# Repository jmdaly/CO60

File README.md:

# CO60 PCB

The CO60 was developed out of the desire to produce a 60% PCB that
appeals to many people and is readily available. CO60 is a portmanteau
of Community and 60% keyboard.

## Overview

The CO60 aims to meet the following design goals:

* Switches oriented such that the LEDs are South-facing, for
  compatibility with Cherry profile keycaps.

* USB Type-C support in both A to C and C to C configurations.

* QMK support.

* A variety of split spacebar configurations, including split 6.25U
  space and split 7U space.

* ESD protection circuitry, including data line protection and a
  polyfuse on the VCC line.

* Support for per-switch LED backlighting.

* Fits in standard 60% keyboard cases.

## Supported Layouts

The CO60 supports the [the following layouts](http://www.keyboard-layout-editor.com/#/gists/b488496b3a71c8192113c07e298be340).

## Motivation

There are a number of 60% keyboard PCBs available today, so it is important to
be clear about the reasons for developing a new one. This PCB is the only 60%
keyboard PCB that, to the best of my knowledge, satisfies ALL of the following
criteria:

* Support for MX switches oriented such that the LEDs are South
  facing, for compatibility with Cherry profile keycaps.

* Support for split spacebars, in both 6.25U and 7U configurations.

* USB Type-C connection that supports both A to C and C to C
  configurations.

* Open source hardware. This allows anybody to do a production run of the board
  at any point, and doesn't lock the design in with a particular vendor.

* QMK support.

* Based on an STM32F303 ARM MCU.

## Obtaining the Files

This repository contains several submodules, which in turn contain
KiCad libraries used in the PCB design. In order to clone the CO60
repository, and all of the library submodules, the following command
must be issued,

```
git clone --recursive https://github.com/jmdaly/CO60.git
```

## Acknowledgements

This PCB design would not have been possible without the help and previous work
of a number of people. In particular, great inspiration has been derived from
the [GH60 project](https://github.com/komar007/gh60), and [ai03's excellent
open source keyboard designs](https://github.com/ai03-2725). This includes the
use of ai03's KiCad [switch footprint
libraries](https://github.com/ai03-2725/MX_Alps_Hybrid.pretty) and his [USB
Type-C](https://github.com/ai03-2725/Type-C.pretty) KiCad footprint libraries.

The Banana Split V2 PCB provided inspiration for some of the bottom row
layouts. The Banana Split was the first 60% PCB to popularize the split
spacebar layout, and the folks at [The Van
Keyboards](https://thevankeyboards.com/) deserve a lot of credit for this
development.

The board outline libraries were created by amtra5, and full credit
goes to him for their design.

There is an active keyboard design community on the MechKeys discord. The
users there have been very helpful, and I've learned a significant
amount about PCB design from them.

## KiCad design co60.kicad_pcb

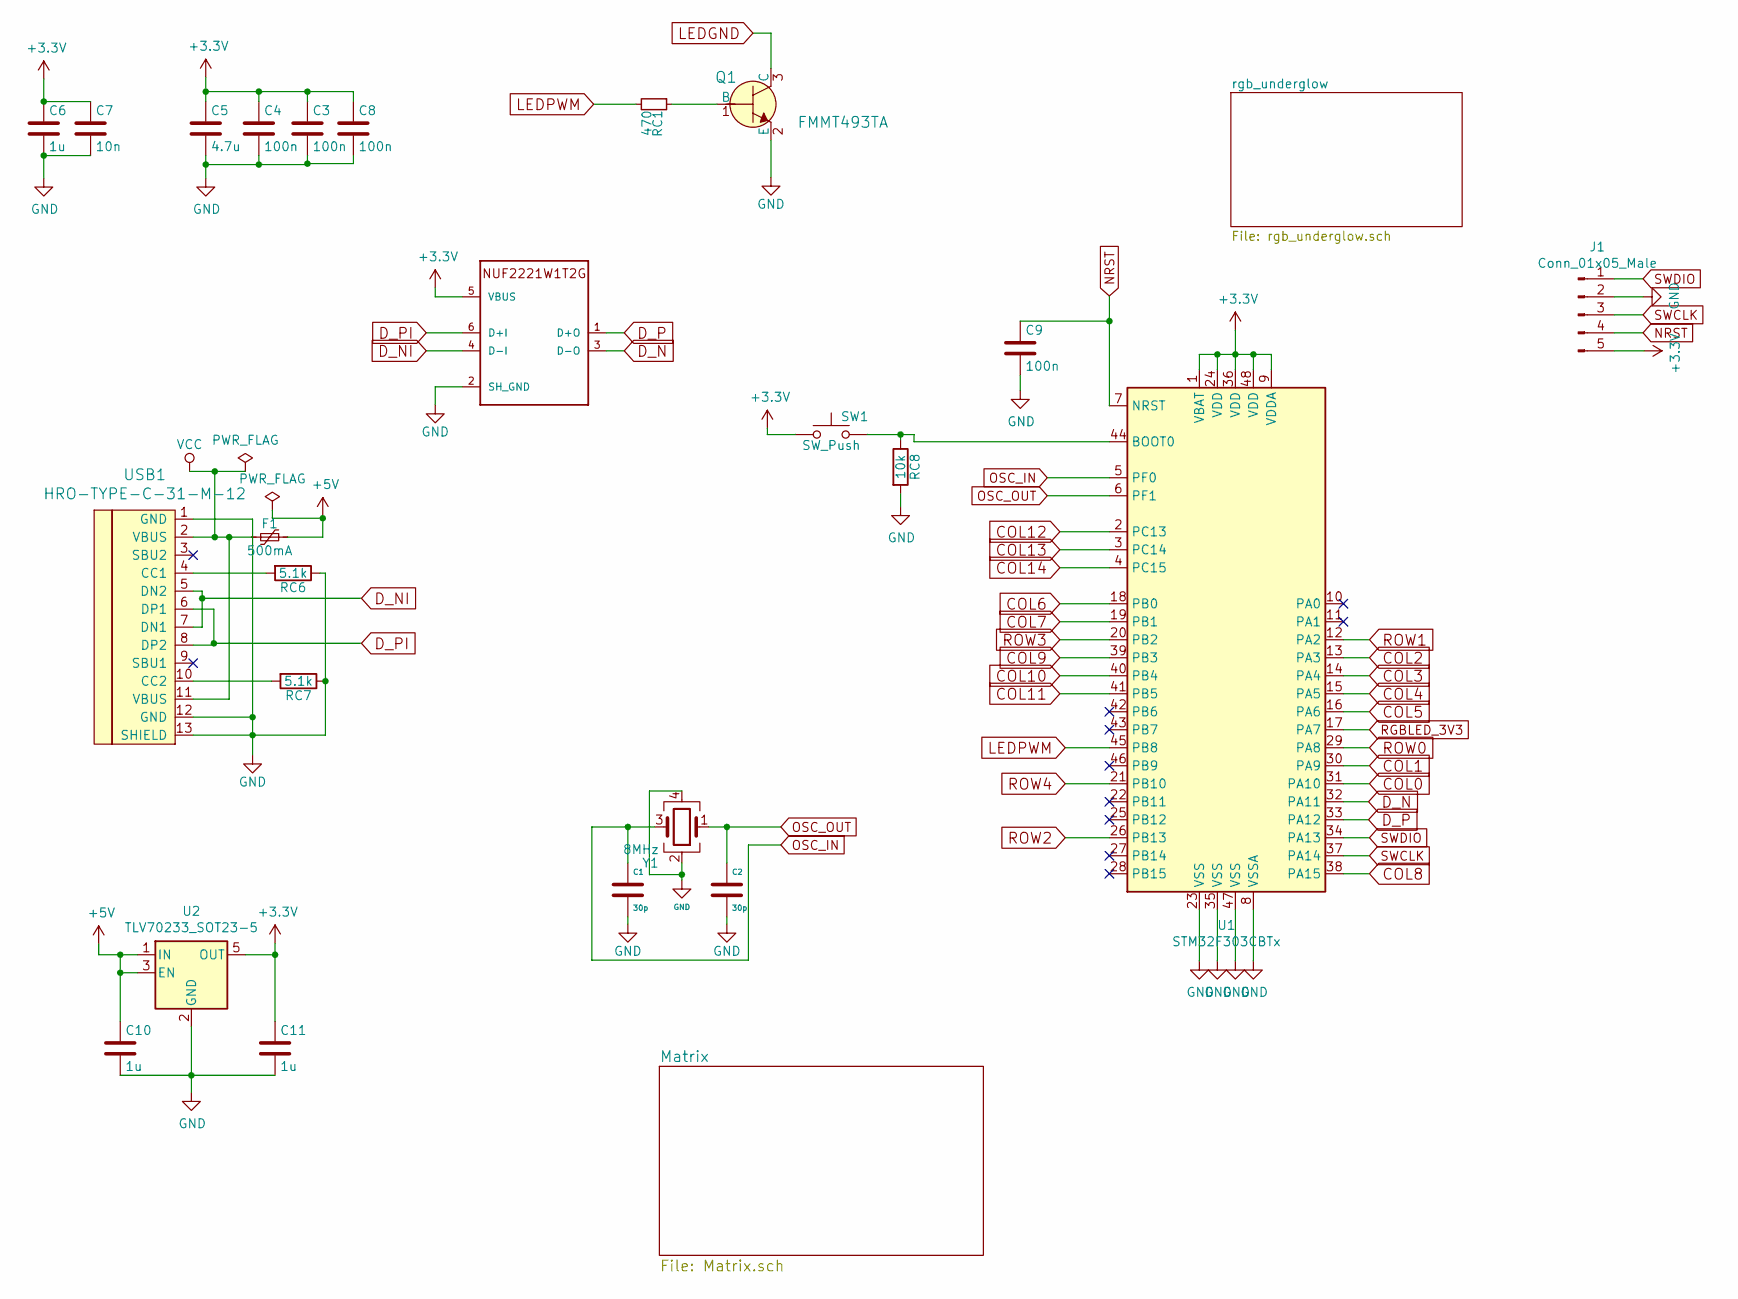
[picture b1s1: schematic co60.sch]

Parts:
C1, C2: 30p; C_0603_1608Metric; LCSC PN C22397
C3, C4, C8, C9: 100n; C_0603_1608Metric; Digi-Key_PN 445-2500-1-ND
C5: 4.7u; C_0603_1608Metric; Digi-Key_PN 1276-1900-1-ND
C6, C10, C11: 1u; C_0603_1608Metric; Digi-Key_PN 445-13234-1-ND
C7: 10n; C_0603_1608Metric; LCSC PN C1589
F1: 500mA; R_0805; Digi-Key_PN F2772CT-ND
J1: Conn_01x05_Male; PinHeader_1x05_P2.54mm_Vertical
Q1: FMMT493TA; SOT-23-3; MPN FMMT493TA; Digi-Key_PN FMMT493CT-ND
RC1: 470; R_0603_1608Metric; LCSC PN C114433
RC6: 5.1k; R_0603; Digi-Key_PN RMCF0603JT5K10CT-ND
RC7: 5.1k; R_0603; LCSC PN C14677
RC8: 10k; R_0603; Digi-Key_PN P10KGCT-ND
SW1: SW_Push; SW_SPST_TL3342; Digi-Key_PN EG2531CT-ND
U1: STM32F303CBTx; LQFP-48_7x7mm_Pitch0.5mm; LCSC PN C108516
U2: TLV70233_SOT23-5; SOT-23-5; LCSC PN C26833
U3: NUF2221W1T2G; SOT-363; LCSC PN C274624
USB1: HRO-TYPE-C-31-M-12; HRO-TYPE-C-31-M-12-Assembly; LCSC PN C165948
Y1: 8MHz; Crystal_SMD_5032-4pin_5.0x3.2mm; LCSC PN C133333

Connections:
+3V3: C3.1, C4.1, C5.1, C6.1, C7.1, C8.1, C11.1, J1.5, SW1.1, U1.1 (VBAT), U1.9 (VDDA), U1.24 (VDD), U1.36 (VDD), U1.48 (VDD), U2.5 (OUT), U3.5 (VBUS)
+5V: C10.1, F1.1, U2.1 (IN), U2.3 (EN); also elsewhere on the board
COL0: U1.31 (PA10); also elsewhere on the board
COL1: U1.30 (PA9); also elsewhere on the board
COL2: U1.13 (PA3); also elsewhere on the board
COL3: U1.14 (PA4); also elsewhere on the board
COL4: U1.15 (PA5); also elsewhere on the board
COL5: U1.16 (PA6); also elsewhere on the board
COL6: U1.18 (PB0); also elsewhere on the board
COL7: U1.19 (PB1); also elsewhere on the board
COL8: U1.38 (PA15); also elsewhere on the board
COL9: U1.39 (PB3); also elsewhere on the board
COL10: U1.40 (PB4); also elsewhere on the board
COL11: U1.41 (PB5); also elsewhere on the board
COL12: U1.2 (PC13); also elsewhere on the board
COL13: U1.3 (PC14); also elsewhere on the board
COL14: U1.4 (PC15); also elsewhere on the board
D_N: U1.32 (PA11), U3.3 (D-O)
D_NI: U3.4 (D-I), USB1.5 (DN2), USB1.7 (DN1)
D_P: U1.33 (PA12), U3.1 (D+O)
D_PI: U3.6 (D+I), USB1.6 (DP1), USB1.8 (DP2)
GND: C1.2, C2.2, C3.2, C4.2, C5.2, C6.2, C7.2, C8.2, C9.2, C10.2, C11.2, J1.2, Q1.2 (E), RC6.1, RC7.1, RC8.2, U1.8 (VSSA), U1.23 (VSS), U1.35 (VSS), U1.47 (VSS), U2.2 (GND), U3.2 (SH_GND), USB1.1 (GND), USB1.12 (GND), USB1.13 (SHIELD), Y1.2, Y1.4; also elsewhere on the board
LEDGND: Q1.3 (C); also elsewhere on the board
LEDPWM: RC1.2, U1.45 (PB8)
NRST: C9.1, J1.4, U1.7 (NRST)
unnamed: Q1.1 (B), RC1.1
unnamed: RC6.2, USB1.4 (CC1)
unnamed: RC7.2, USB1.10 (CC2)
unnamed: RC8.1, SW1.2, U1.44 (BOOT0)
OSC_IN: C1.1, U1.5 (PF0), Y1.3
OSC_OUT: C2.1, U1.6 (PF1), Y1.1
RGBLED_3V3: U1.17 (PA7); also elsewhere on the board
ROW0: U1.29 (PA8); also elsewhere on the board
ROW1: U1.12 (PA2); also elsewhere on the board
ROW2: U1.26 (PB13); also elsewhere on the board
ROW3: U1.20 (PB2); also elsewhere on the board
ROW4: U1.21 (PB10); also elsewhere on the board
SWCLK: J1.3, U1.37 (PA14)
SWDIO: J1.1, U1.34 (PA13)
VCC: F1.2, USB1.2 (VBUS), USB1.11 (VBUS)

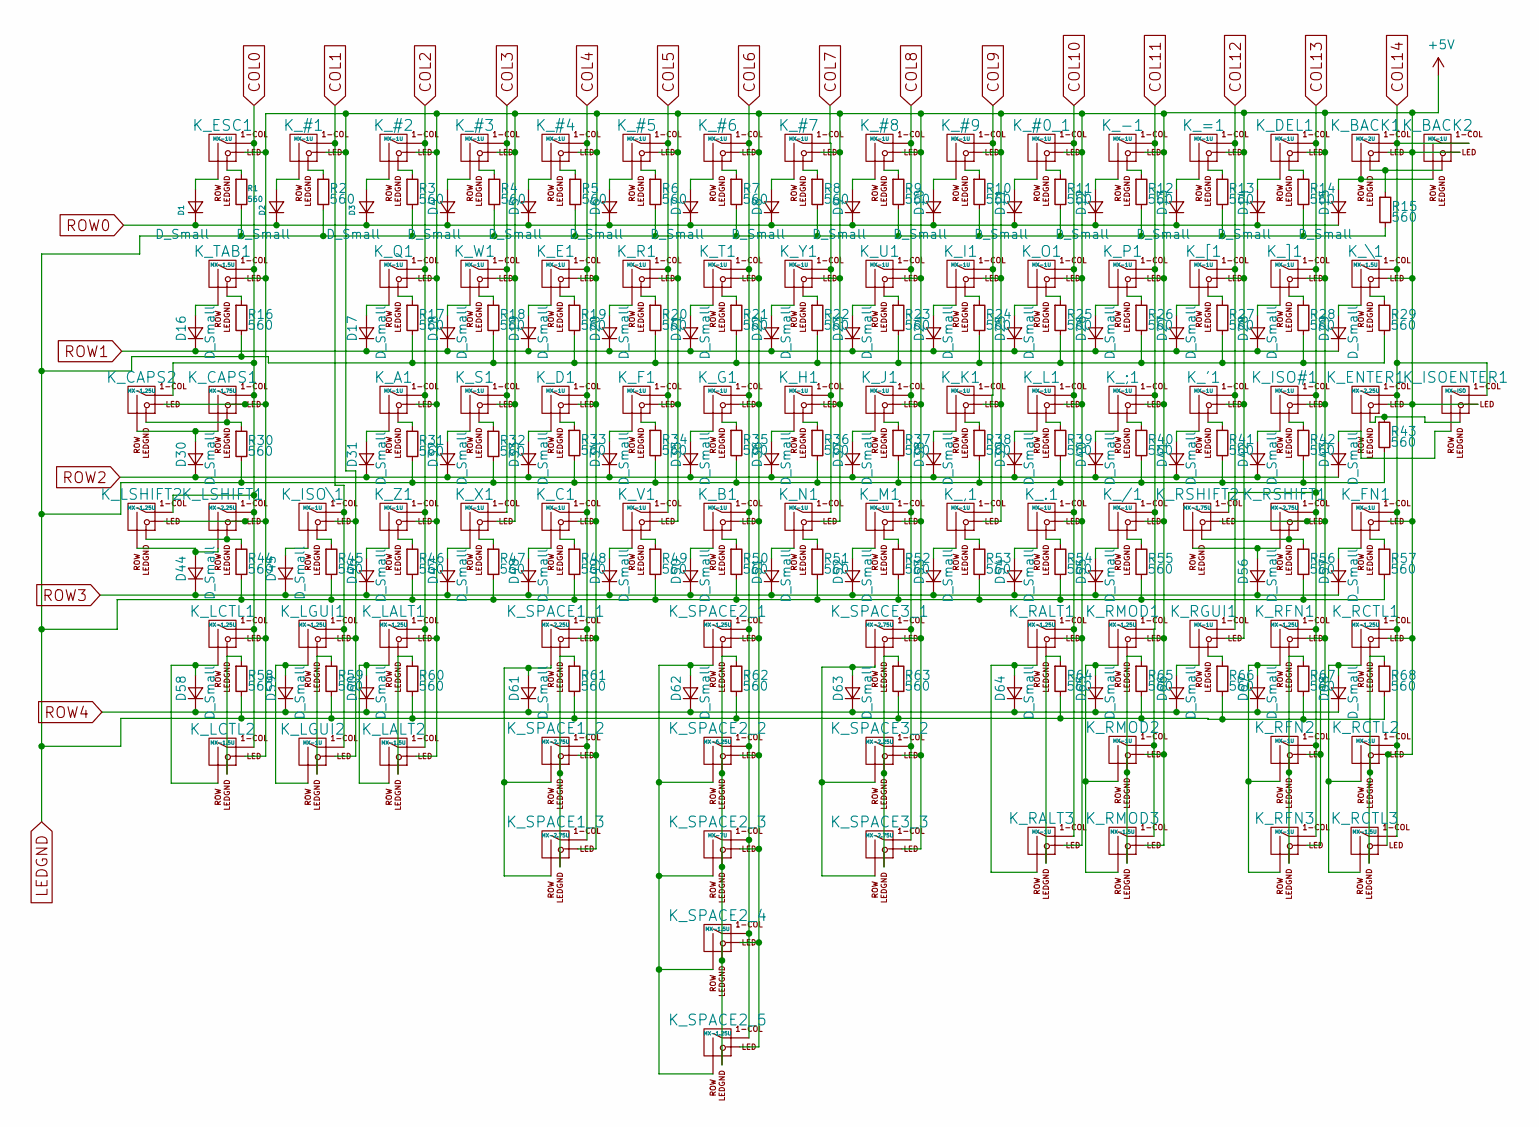
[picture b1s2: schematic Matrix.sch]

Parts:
D1: D_Small; D_SOD-123; Digi-Key_PN 1N4148WTPMSCT-ND
D2, D3, D4, D5, D6, D7, D8, D9, D10, D11, D12, D13, D14, D15, D16, D17, D18, D19, D20, D21, D22, D23, D24, D25, D26, D27, D28, D29, D30, D31, D32, D33, D34, D35, D36, D37, D38, D39, D40, D41, D42, D43, D44, D45, D46, D47, D48, D49, D50, D51, D52, D53, D54, D55, D56, D57, D58, D59, D60, D61, D62, D63, D64, D65, D66, D67, D68: D_Small; D_SOD-123
K_#0_1, K_#1, K_#2, K_#3, K_#4, K_#5, K_#6, K_#7, K_#8, K_#9: MX-1U; MXOnly-1U-FLIPPED
K_'1: MX-1U; MXOnly-1U-FLIPPED
K_,1: MX-1U; MXOnly-1U-FLIPPED
K_-1: MX-1U; MXOnly-1U-FLIPPED
K_.1: MX-1U; MXOnly-1U-FLIPPED
K_/1: MX-1U; MXOnly-1U-FLIPPED
K_;1: MX-1U; MXOnly-1U-FLIPPED
K_=1: MX-1U; MXOnly-1U-FLIPPED
K_A1: MX-1U; MXOnly-1U-FLIPPED
K_B1: MX-1U; MXOnly-1U-FLIPPED
K_BACK1: MX-2U; MXOnly-2U-FLIPPED
K_BACK2: MX-1U; MXOnly-1U-FLIPPED
K_C1: MX-1U; MXOnly-1U-FLIPPED
K_CAPS1: MX-1.75U; MXOnly-1.75U
K_CAPS2: MX-1.25U; MXOnly-1.25U-FLIPPED
K_D1: MX-1U; MXOnly-1U-FLIPPED
K_DEL1: MX-1U; MXOnly-1U-FLIPPED
K_E1: MX-1U; MXOnly-1U-FLIPPED
K_ENTER1: MX-2.25U; MXOnly-2.25U-FLIPPED
K_ESC1: MX-1U; MXOnly-1U-FLIPPED
K_F1: MX-1U; MXOnly-1U-FLIPPED
K_FN1: MX-1U; MXOnly-1U-FLIPPED
K_G1: MX-1U; MXOnly-1U-FLIPPED
K_H1: MX-1U; MXOnly-1U-FLIPPED
K_I1: MX-1U; MXOnly-1U-FLIPPED
K_ISO#1: MX-1U; MXOnly-1U-FLIPPED
K_ISOENTER1: MX-ISO; MXOnly-ISO-ROTATED-ReversedStabilizers
K_ISO\1: MX-1U; MXOnly-1U-FLIPPED
K_J1: MX-1U; MXOnly-1U-FLIPPED
K_K1: MX-1U; MXOnly-1U-FLIPPED
K_L1: MX-1U; MXOnly-1U-FLIPPED
K_LALT1: MX-1.25U; MXOnly-1.25U-FLIPPED
K_LALT2: MX-1.5U; MXOnly-1.5U
K_LCTL1: MX-1.25U; MXOnly-1.25U-FLIPPED
K_LCTL2: MX-1.5U; MXOnly-1.5U
K_LGUI1: MX-1.25U; MXOnly-1.25U-FLIPPED
K_LGUI2: MX-1U; MXOnly-1U
K_LSHIFT1: MX-2.25U; MXOnly-2.25U-FLIPPED
K_LSHIFT2: MX-1.25U; MXOnly-1.25U-FLIPPED
K_M1: MX-1U; MXOnly-1U-FLIPPED
K_N1: MX-1U; MXOnly-1U-FLIPPED
K_O1: MX-1U; MXOnly-1U-FLIPPED
K_P1: MX-1U; MXOnly-1U-FLIPPED
K_Q1: MX-1U; MXOnly-1U-FLIPPED
K_R1: MX-1U; MXOnly-1U-FLIPPED
K_RALT1: MX-1.25U; MXOnly-1.25U-FLIPPED
K_RALT3: MX-1U; MXOnly-1U
K_RCTL1: MX-1.25U; MXOnly-1.25U-FLIPPED
K_RCTL2: MX-1U; MXOnly-1U
K_RCTL3: MX-1.5U; MXOnly-1.5U
K_RFN1: MX-1.25U; MXOnly-1.25U-FLIPPED
K_RFN2, K_RFN3: MX-1U; MXOnly-1U
K_RGUI1: MX-1U; MXOnly-1U-FLIPPED
K_RMOD1: MX-1.25U; MXOnly-1.25U
K_RMOD2: MX-1U; MXOnly-1U
K_RMOD3: MX-1.5U; MXOnly-1.5U-FLIPPED
K_RSHIFT1: MX-2.75U; MXOnly-2.75U-FLIPPED
K_RSHIFT2: MX-1.75U; MXOnly-1.75U-FLIPPED
K_S1: MX-1U; MXOnly-1U-FLIPPED
K_SPACE1_1, K_SPACE3_2: MX-2.25U; MXOnly-2.25U-ReversedStabilizers
K_SPACE1_2, K_SPACE3_1: MX-2.75U; MXOnly-2.75U-FLIPPED-ReversedStabilizers
K_SPACE1_3, K_SPACE3_3: MX-2.75U; MXOnly-2.75U-ReversedStabilizers
K_SPACE2_1, K_SPACE2_5: MX-1.25U; MXOnly-1.25U-FLIPPED
K_SPACE2_2: MX-6.25U; MXOnly-6.25U-ReversedStabilizers
K_SPACE2_3: MX-7U; MXOnly-7U-ReversedStabilizers
K_SPACE2_4: MX-1.5U; MXOnly-1.5U
K_T1: MX-1U; MXOnly-1U-FLIPPED
K_TAB1: MX-1.5U; MXOnly-1.5U-FLIPPED
K_U1: MX-1U; MXOnly-1U-FLIPPED
K_V1: MX-1U; MXOnly-1U-FLIPPED
K_W1: MX-1U; MXOnly-1U-FLIPPED
K_X1: MX-1U; MXOnly-1U-FLIPPED
K_Y1: MX-1U; MXOnly-1U-FLIPPED
K_Z1: MX-1U; MXOnly-1U-FLIPPED
K_[1: MX-1U; MXOnly-1U-FLIPPED
K_\1: MX-1.5U; MXOnly-1.5U-FLIPPED
K_]1: MX-1U; MXOnly-1U-FLIPPED
R1: 560; R_0603; Digi-Key_PN MCT0603-560-CFCT-ND
R2, R3, R4, R5, R6, R7, R8, R9, R10, R11, R12, R13, R14, R15, R16, R17, R18, R19, R20, R21, R22, R23, R24, R25, R26, R27, R28, R29, R30, R31, R32, R33, R34, R35, R36, R37, R38, R39, R40, R41, R42, R43, R44, R45, R46, R47, R48, R49, R50, R51, R52, R53, R54, R55, R56, R57, R58, R59, R60, R61, R62, R63, R64, R65, R66, R67, R68: 560; R_0603

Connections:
+5V: K_#0_1.3 (LED), K_#1.3 (LED), K_#2.3 (LED), K_#3.3 (LED), K_#4.3 (LED), K_#5.3 (LED), K_#6.3 (LED), K_#7.3 (LED), K_#8.3 (LED), K_#9.3 (LED), K_'1.3 (LED), K_,1.3 (LED), K_-1.3 (LED), K_.1.3 (LED), K_/1.3 (LED), K_;1.3 (LED), K_=1.3 (LED), K_A1.3 (LED), K_B1.3 (LED), K_BACK1.3 (LED), K_BACK2.3 (LED), K_C1.3 (LED), K_CAPS1.3 (LED), K_CAPS2.3 (LED), K_D1.3 (LED), K_DEL1.3 (LED), K_E1.3 (LED), K_ENTER1.3 (LED), K_ESC1.3 (LED), K_F1.3 (LED), K_FN1.3 (LED), K_G1.3 (LED), K_H1.3 (LED), K_I1.3 (LED), K_ISO#1.3 (LED), K_ISOENTER1.3 (LED), K_ISO\1.3 (LED), K_J1.3 (LED), K_K1.3 (LED), K_L1.3 (LED), K_LALT1.3 (LED), K_LALT2.3 (LED), K_LCTL1.3 (LED), K_LCTL2.3 (LED), K_LGUI1.3 (LED), K_LGUI2.3 (LED), K_LSHIFT1.3 (LED), K_LSHIFT2.3 (LED), K_M1.3 (LED), K_N1.3 (LED), K_O1.3 (LED), K_P1.3 (LED), K_Q1.3 (LED), K_R1.3 (LED), K_RALT1.3 (LED), K_RALT3.3 (LED), K_RCTL1.3 (LED), K_RCTL2.3 (LED), K_RCTL3.3 (LED), K_RFN1.3 (LED), K_RFN2.3 (LED), K_RFN3.3 (LED), K_RGUI1.3 (LED), K_RMOD1.3 (LED), K_RMOD2.3 (LED), K_RMOD3.3 (LED), K_RSHIFT1.3 (LED), K_RSHIFT2.3 (LED), K_S1.3 (LED), K_SPACE1_1.3 (LED), K_SPACE1_2.3 (LED), K_SPACE1_3.3 (LED), K_SPACE2_1.3 (LED), K_SPACE2_2.3 (LED), K_SPACE2_3.3 (LED), K_SPACE2_4.3 (LED), K_SPACE2_5.3 (LED), K_SPACE3_1.3 (LED), K_SPACE3_2.3 (LED), K_SPACE3_3.3 (LED), K_T1.3 (LED), K_TAB1.3 (LED), K_U1.3 (LED), K_V1.3 (LED), K_W1.3 (LED), K_X1.3 (LED), K_Y1.3 (LED), K_Z1.3 (LED), K_[1.3 (LED), K_\1.3 (LED), K_]1.3 (LED); also elsewhere on the board
COL0: K_CAPS1.1 (COL), K_CAPS2.1 (COL), K_ESC1.1 (COL), K_LCTL1.1 (COL), K_LCTL2.1 (COL), K_LSHIFT1.1 (COL), K_LSHIFT2.1 (COL), K_TAB1.1 (COL); also elsewhere on the board
COL1: K_#1.1 (COL), K_ISO\1.1 (COL), K_LGUI1.1 (COL), K_LGUI2.1 (COL); also elsewhere on the board
COL2: K_#2.1 (COL), K_A1.1 (COL), K_LALT1.1 (COL), K_LALT2.1 (COL), K_Q1.1 (COL), K_Z1.1 (COL); also elsewhere on the board
COL3: K_#3.1 (COL), K_S1.1 (COL), K_W1.1 (COL), K_X1.1 (COL); also elsewhere on the board
COL4: K_#4.1 (COL), K_C1.1 (COL), K_D1.1 (COL), K_E1.1 (COL), K_SPACE1_1.1 (COL), K_SPACE1_2.1 (COL), K_SPACE1_3.1 (COL); also elsewhere on the board
COL5: K_#5.1 (COL), K_F1.1 (COL), K_R1.1 (COL), K_V1.1 (COL); also elsewhere on the board
COL6: K_#6.1 (COL), K_B1.1 (COL), K_G1.1 (COL), K_SPACE2_1.1 (COL), K_SPACE2_2.1 (COL), K_SPACE2_3.1 (COL), K_SPACE2_4.1 (COL), K_SPACE2_5.1 (COL), K_T1.1 (COL); also elsewhere on the board
COL7: K_#7.1 (COL), K_H1.1 (COL), K_N1.1 (COL), K_Y1.1 (COL); also elsewhere on the board
COL8: K_#8.1 (COL), K_J1.1 (COL), K_M1.1 (COL), K_SPACE3_1.1 (COL), K_SPACE3_2.1 (COL), K_SPACE3_3.1 (COL), K_U1.1 (COL); also elsewhere on the board
COL9: K_#9.1 (COL), K_,1.1 (COL), K_I1.1 (COL), K_K1.1 (COL); also elsewhere on the board
COL10: K_#0_1.1 (COL), K_.1.1 (COL), K_L1.1 (COL), K_O1.1 (COL), K_RALT1.1 (COL), K_RALT3.1 (COL); also elsewhere on the board
COL11: K_-1.1 (COL), K_/1.1 (COL), K_;1.1 (COL), K_P1.1 (COL), K_RMOD1.1 (COL), K_RMOD2.1 (COL), K_RMOD3.1 (COL); also elsewhere on the board
COL12: K_'1.1 (COL), K_=1.1 (COL), K_RGUI1.1 (COL), K_[1.1 (COL); also elsewhere on the board
COL13: K_DEL1.1 (COL), K_ISO#1.1 (COL), K_RFN1.1 (COL), K_RFN2.1 (COL), K_RFN3.1 (COL), K_RSHIFT1.1 (COL), K_RSHIFT2.1 (COL), K_]1.1 (COL); also elsewhere on the board
COL14: K_BACK1.1 (COL), K_BACK2.1 (COL), K_ENTER1.1 (COL), K_FN1.1 (COL), K_ISOENTER1.1 (COL), K_RCTL1.1 (COL), K_RCTL2.1 (COL), K_RCTL3.1 (COL), K_\1.1 (COL); also elsewhere on the board
LEDGND: R1.2, R2.2, R3.2, R4.2, R5.2, R6.2, R7.2, R8.2, R9.2, R10.2, R11.2, R12.2, R13.2, R14.2, R15.2, R16.2, R17.2, R18.2, R19.2, R20.2, R21.2, R22.2, R23.2, R24.2, R25.2, R26.2, R27.2, R28.2, R29.2, R30.2, R31.2, R32.2, R33.2, R34.2, R35.2, R36.2, R37.2, R38.2, R39.2, R40.2, R41.2, R42.2, R43.2, R44.2, R45.2, R46.2, R47.2, R48.2, R49.2, R50.2, R51.2, R52.2, R53.2, R54.2, R55.2, R56.2, R57.2, R58.2, R59.2, R60.2, R61.2, R62.2, R63.2, R64.2, R65.2, R66.2, R67.2, R68.2; also elsewhere on the board
unnamed: D1.2 (A), K_ESC1.2 (ROW)
unnamed: D2.2 (A), K_#1.2 (ROW)
unnamed: D3.2 (A), K_#2.2 (ROW)
unnamed: D4.2 (A), K_#3.2 (ROW)
unnamed: D5.2 (A), K_#4.2 (ROW)
unnamed: D6.2 (A), K_#5.2 (ROW)
unnamed: D7.2 (A), K_#6.2 (ROW)
unnamed: D8.2 (A), K_#7.2 (ROW)
unnamed: D9.2 (A), K_#8.2 (ROW)
unnamed: D10.2 (A), K_#9.2 (ROW)
unnamed: D11.2 (A), K_#0_1.2 (ROW)
unnamed: D12.2 (A), K_-1.2 (ROW)
unnamed: D13.2 (A), K_=1.2 (ROW)
unnamed: D14.2 (A), K_DEL1.2 (ROW)
unnamed: D15.2 (A), K_BACK1.2 (ROW), K_BACK2.2 (ROW)
unnamed: D16.2 (A), K_TAB1.2 (ROW)
unnamed: D17.2 (A), K_Q1.2 (ROW)
unnamed: D18.2 (A), K_W1.2 (ROW)
unnamed: D19.2 (A), K_E1.2 (ROW)
unnamed: D20.2 (A), K_R1.2 (ROW)
unnamed: D21.2 (A), K_T1.2 (ROW)
unnamed: D22.2 (A), K_Y1.2 (ROW)
unnamed: D23.2 (A), K_U1.2 (ROW)
unnamed: D24.2 (A), K_I1.2 (ROW)
unnamed: D25.2 (A), K_O1.2 (ROW)
unnamed: D26.2 (A), K_P1.2 (ROW)
unnamed: D27.2 (A), K_[1.2 (ROW)
unnamed: D28.2 (A), K_]1.2 (ROW)
unnamed: D29.2 (A), K_\1.2 (ROW)
unnamed: D30.2 (A), K_CAPS1.2 (ROW), K_CAPS2.2 (ROW)
unnamed: D31.2 (A), K_A1.2 (ROW)
unnamed: D32.2 (A), K_S1.2 (ROW)
unnamed: D33.2 (A), K_D1.2 (ROW)
unnamed: D34.2 (A), K_F1.2 (ROW)
unnamed: D35.2 (A), K_G1.2 (ROW)
unnamed: D36.2 (A), K_H1.2 (ROW)
unnamed: D37.2 (A), K_J1.2 (ROW)
unnamed: D38.2 (A), K_K1.2 (ROW)
unnamed: D39.2 (A), K_L1.2 (ROW)
unnamed: D40.2 (A), K_;1.2 (ROW)
unnamed: D41.2 (A), K_'1.2 (ROW)
unnamed: D42.2 (A), K_ISO#1.2 (ROW)
unnamed: D43.2 (A), K_ENTER1.2 (ROW), K_ISOENTER1.2 (ROW)
unnamed: D44.2 (A), K_LSHIFT1.2 (ROW), K_LSHIFT2.2 (ROW)
unnamed: D45.2 (A), K_ISO\1.2 (ROW)
unnamed: D46.2 (A), K_Z1.2 (ROW)
unnamed: D47.2 (A), K_X1.2 (ROW)
unnamed: D48.2 (A), K_C1.2 (ROW)
unnamed: D49.2 (A), K_V1.2 (ROW)
unnamed: D50.2 (A), K_B1.2 (ROW)
unnamed: D51.2 (A), K_N1.2 (ROW)
unnamed: D52.2 (A), K_M1.2 (ROW)
unnamed: D53.2 (A), K_,1.2 (ROW)
unnamed: D54.2 (A), K_.1.2 (ROW)
unnamed: D55.2 (A), K_/1.2 (ROW)
unnamed: D56.2 (A), K_RSHIFT1.2 (ROW), K_RSHIFT2.2 (ROW)
unnamed: D57.2 (A), K_FN1.2 (ROW)
unnamed: D58.2 (A), K_LCTL1.2 (ROW), K_LCTL2.2 (ROW)
unnamed: D59.2 (A), K_LGUI1.2 (ROW), K_LGUI2.2 (ROW)
unnamed: D60.2 (A), K_LALT1.2 (ROW), K_LALT2.2 (ROW)
unnamed: D61.2 (A), K_SPACE1_1.2 (ROW), K_SPACE1_2.2 (ROW), K_SPACE1_3.2 (ROW)
unnamed: D62.2 (A), K_SPACE2_1.2 (ROW), K_SPACE2_2.2 (ROW), K_SPACE2_3.2 (ROW), K_SPACE2_4.2 (ROW), K_SPACE2_5.2 (ROW)
unnamed: D63.2 (A), K_SPACE3_1.2 (ROW), K_SPACE3_2.2 (ROW), K_SPACE3_3.2 (ROW)
unnamed: D64.2 (A), K_RALT1.2 (ROW), K_RALT3.2 (ROW)
unnamed: D65.2 (A), K_RMOD1.2 (ROW), K_RMOD2.2 (ROW), K_RMOD3.2 (ROW)
unnamed: D66.2 (A), K_RGUI1.2 (ROW)
unnamed: D67.2 (A), K_RFN1.2 (ROW), K_RFN2.2 (ROW), K_RFN3.2 (ROW)
unnamed: D68.2 (A), K_RCTL1.2 (ROW), K_RCTL2.2 (ROW), K_RCTL3.2 (ROW)
unnamed: K_#0_1.4 (LEDGND), R11.1
unnamed: K_#1.4 (LEDGND), R2.1
unnamed: K_#2.4 (LEDGND), R3.1
unnamed: K_#3.4 (LEDGND), R4.1
unnamed: K_#4.4 (LEDGND), R5.1
unnamed: K_#5.4 (LEDGND), R6.1
unnamed: K_#6.4 (LEDGND), R7.1
unnamed: K_#7.4 (LEDGND), R8.1
unnamed: K_#8.4 (LEDGND), R9.1
unnamed: K_#9.4 (LEDGND), R10.1
unnamed: K_'1.4 (LEDGND), R41.1
unnamed: K_,1.4 (LEDGND), R53.1
unnamed: K_-1.4 (LEDGND), R12.1
unnamed: K_.1.4 (LEDGND), R54.1
unnamed: K_/1.4 (LEDGND), R55.1
unnamed: K_;1.4 (LEDGND), R40.1
unnamed: K_=1.4 (LEDGND), R13.1
unnamed: K_A1.4 (LEDGND), R31.1
unnamed: K_B1.4 (LEDGND), R50.1
unnamed: K_BACK1.4 (LEDGND), K_BACK2.4 (LEDGND), R15.1
unnamed: K_C1.4 (LEDGND), R48.1
unnamed: K_CAPS1.4 (LEDGND), K_CAPS2.4 (LEDGND), R30.1
unnamed: K_D1.4 (LEDGND), R33.1
unnamed: K_DEL1.4 (LEDGND), R14.1
unnamed: K_E1.4 (LEDGND), R19.1
unnamed: K_ENTER1.4 (LEDGND), K_ISOENTER1.4 (LEDGND), R43.1
unnamed: K_ESC1.4 (LEDGND), R1.1
unnamed: K_F1.4 (LEDGND), R34.1
unnamed: K_FN1.4 (LEDGND), R57.1
unnamed: K_G1.4 (LEDGND), R35.1
unnamed: K_H1.4 (LEDGND), R36.1
unnamed: K_I1.4 (LEDGND), R24.1
unnamed: K_ISO#1.4 (LEDGND), R42.1
unnamed: K_ISO\1.4 (LEDGND), R45.1
unnamed: K_J1.4 (LEDGND), R37.1
unnamed: K_K1.4 (LEDGND), R38.1
unnamed: K_L1.4 (LEDGND), R39.1
unnamed: K_LALT1.4 (LEDGND), K_LALT2.4 (LEDGND), R60.1
unnamed: K_LCTL1.4 (LEDGND), K_LCTL2.4 (LEDGND), R58.1
unnamed: K_LGUI1.4 (LEDGND), K_LGUI2.4 (LEDGND), R59.1
unnamed: K_LSHIFT1.4 (LEDGND), K_LSHIFT2.4 (LEDGND), R44.1
unnamed: K_M1.4 (LEDGND), R52.1
unnamed: K_N1.4 (LEDGND), R51.1
unnamed: K_O1.4 (LEDGND), R25.1
unnamed: K_P1.4 (LEDGND), R26.1
unnamed: K_Q1.4 (LEDGND), R17.1
unnamed: K_R1.4 (LEDGND), R20.1
unnamed: K_RALT1.4 (LEDGND), K_RALT3.4 (LEDGND), R64.1
unnamed: K_RCTL1.4 (LEDGND), K_RCTL2.4 (LEDGND), K_RCTL3.4 (LEDGND), R68.1
unnamed: K_RFN1.4 (LEDGND), K_RFN2.4 (LEDGND), K_RFN3.4 (LEDGND), R67.1
unnamed: K_RGUI1.4 (LEDGND), R66.1
unnamed: K_RMOD1.4 (LEDGND), K_RMOD2.4 (LEDGND), K_RMOD3.4 (LEDGND), R65.1
unnamed: K_RSHIFT1.4 (LEDGND), K_RSHIFT2.4 (LEDGND), R56.1
unnamed: K_S1.4 (LEDGND), R32.1
unnamed: K_SPACE1_1.4 (LEDGND), K_SPACE1_2.4 (LEDGND), K_SPACE1_3.4 (LEDGND), R61.1
unnamed: K_SPACE2_1.4 (LEDGND), K_SPACE2_2.4 (LEDGND), K_SPACE2_3.4 (LEDGND), K_SPACE2_4.4 (LEDGND), K_SPACE2_5.4 (LEDGND), R62.1
unnamed: K_SPACE3_1.4 (LEDGND), K_SPACE3_2.4 (LEDGND), K_SPACE3_3.4 (LEDGND), R63.1
unnamed: K_T1.4 (LEDGND), R21.1
unnamed: K_TAB1.4 (LEDGND), R16.1
unnamed: K_U1.4 (LEDGND), R23.1
unnamed: K_V1.4 (LEDGND), R49.1
unnamed: K_W1.4 (LEDGND), R18.1
unnamed: K_X1.4 (LEDGND), R47.1
unnamed: K_Y1.4 (LEDGND), R22.1
unnamed: K_Z1.4 (LEDGND), R46.1
unnamed: K_[1.4 (LEDGND), R27.1
unnamed: K_\1.4 (LEDGND), R29.1
unnamed: K_]1.4 (LEDGND), R28.1
ROW0: D1.1 (K), D2.1 (K), D3.1 (K), D4.1 (K), D5.1 (K), D6.1 (K), D7.1 (K), D8.1 (K), D9.1 (K), D10.1 (K), D11.1 (K), D12.1 (K), D13.1 (K), D14.1 (K), D15.1 (K); also elsewhere on the board
ROW1: D16.1 (K), D17.1 (K), D18.1 (K), D19.1 (K), D20.1 (K), D21.1 (K), D22.1 (K), D23.1 (K), D24.1 (K), D25.1 (K), D26.1 (K), D27.1 (K), D28.1 (K), D29.1 (K); also elsewhere on the board
ROW2: D30.1 (K), D31.1 (K), D32.1 (K), D33.1 (K), D34.1 (K), D35.1 (K), D36.1 (K), D37.1 (K), D38.1 (K), D39.1 (K), D40.1 (K), D41.1 (K), D42.1 (K), D43.1 (K); also elsewhere on the board
ROW3: D44.1 (K), D45.1 (K), D46.1 (K), D47.1 (K), D48.1 (K), D49.1 (K), D50.1 (K), D51.1 (K), D52.1 (K), D53.1 (K), D54.1 (K), D55.1 (K), D56.1 (K), D57.1 (K); also elsewhere on the board
ROW4: D58.1 (K), D59.1 (K), D60.1 (K), D61.1 (K), D62.1 (K), D63.1 (K), D64.1 (K), D65.1 (K), D66.1 (K), D67.1 (K), D68.1 (K); also elsewhere on the board

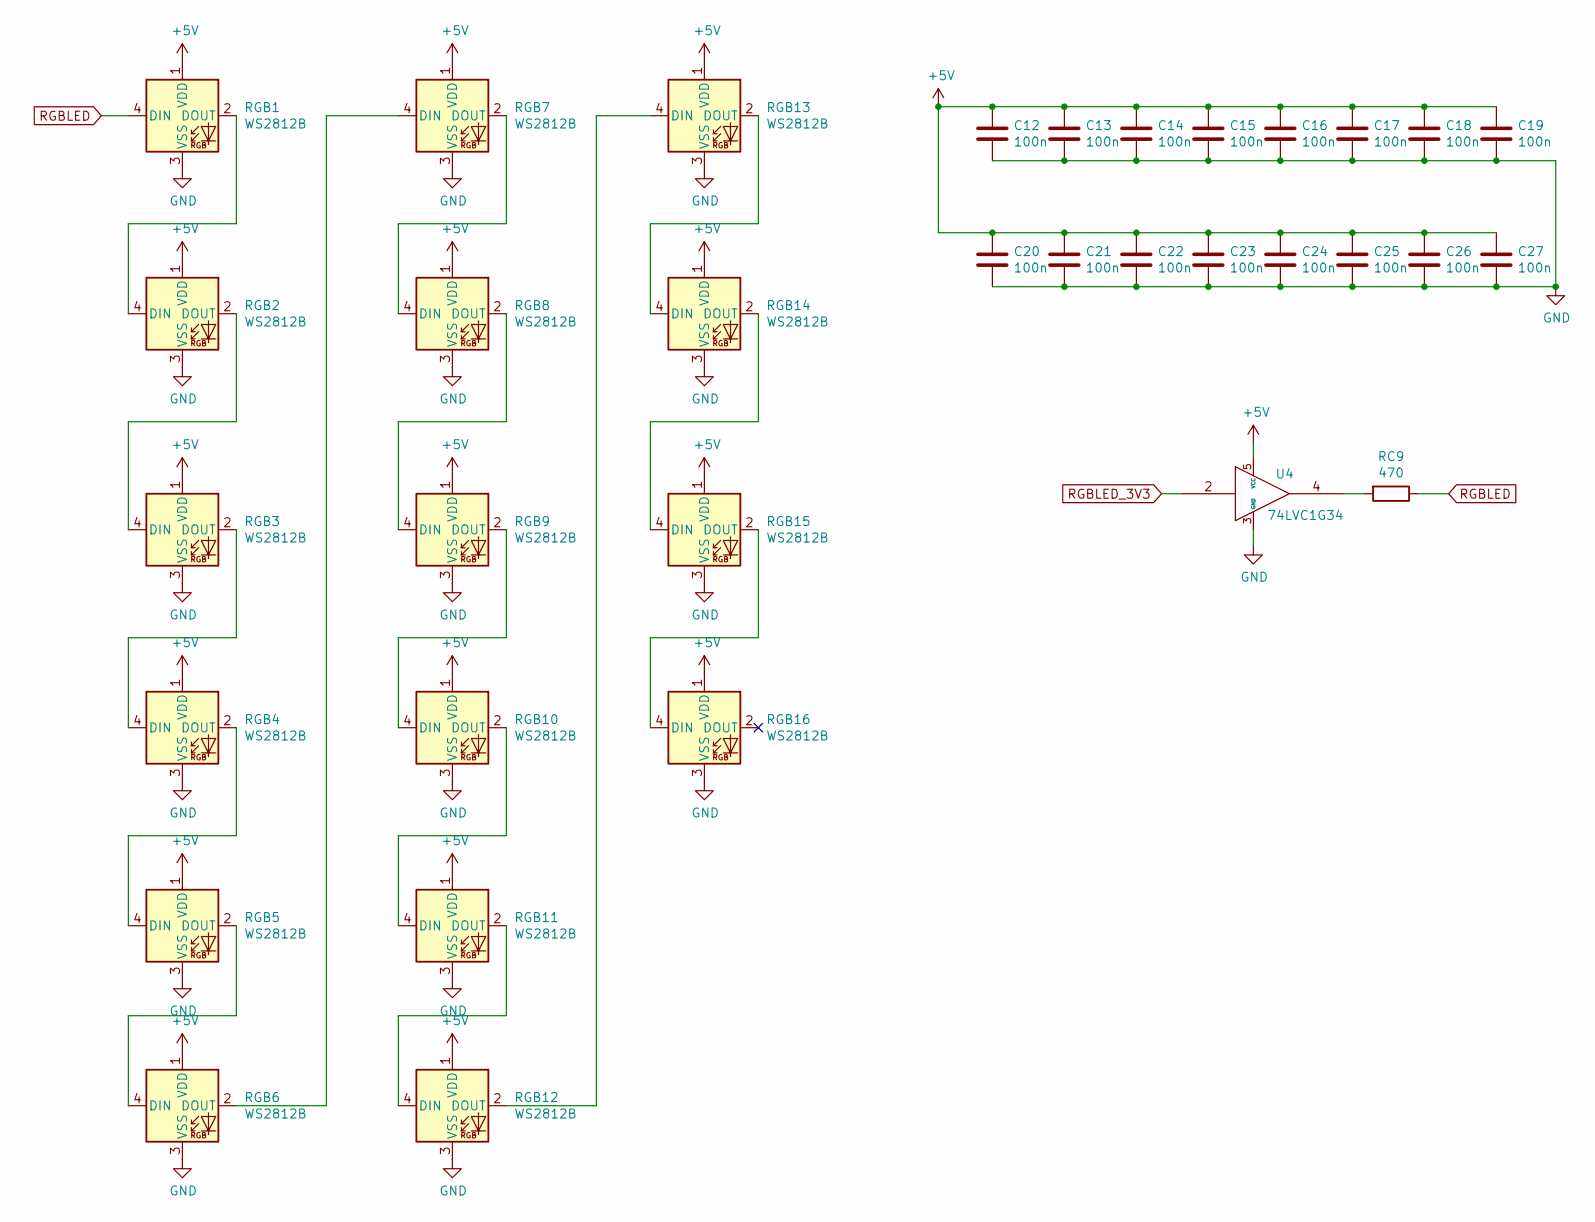
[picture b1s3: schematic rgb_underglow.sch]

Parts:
C12, C13, C14, C15, C16, C17, C18, C19, C20, C21, C22, C23, C24, C25, C26, C27: 100n; C_0603_1608Metric; LCSC PN C1590
RC9: 470; R_0603_1608Metric; LCSC PN C114433
RGB1, RGB2, RGB3, RGB4, RGB5, RGB6, RGB7, RGB8, RGB9, RGB10, RGB11, RGB12, RGB13, RGB14, RGB15, RGB16: WS2812B; LED_WS2812B_PLCC4_5.0x5.0mm_P3.2mm; LCSC PN C114585
U4: 74LVC1G34; SOT-353_SC-70-5; LCSC PN C94111

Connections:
+5V: C12.1, C13.1, C14.1, C15.1, C16.1, C17.1, C18.1, C19.1, C20.1, C21.1, C22.1, C23.1, C24.1, C25.1, C26.1, C27.1, RGB1.1 (VDD), RGB2.1 (VDD), RGB3.1 (VDD), RGB4.1 (VDD), RGB5.1 (VDD), RGB6.1 (VDD), RGB7.1 (VDD), RGB8.1 (VDD), RGB9.1 (VDD), RGB10.1 (VDD), RGB11.1 (VDD), RGB12.1 (VDD), RGB13.1 (VDD), RGB14.1 (VDD), RGB15.1 (VDD), RGB16.1 (VDD), U4.5 (VCC); also elsewhere on the board
GND: C12.2, C13.2, C14.2, C15.2, C16.2, C17.2, C18.2, C19.2, C20.2, C21.2, C22.2, C23.2, C24.2, C25.2, C26.2, C27.2, RGB1.3 (VSS), RGB2.3 (VSS), RGB3.3 (VSS), RGB4.3 (VSS), RGB5.3 (VSS), RGB6.3 (VSS), RGB7.3 (VSS), RGB8.3 (VSS), RGB9.3 (VSS), RGB10.3 (VSS), RGB11.3 (VSS), RGB12.3 (VSS), RGB13.3 (VSS), RGB14.3 (VSS), RGB15.3 (VSS), RGB16.3 (VSS), U4.3 (GND); also elsewhere on the board
unnamed: RC9.2, U4.4
unnamed: RGB1.2 (DOUT), RGB2.4 (DIN)
unnamed: RGB2.2 (DOUT), RGB3.4 (DIN)
unnamed: RGB3.2 (DOUT), RGB4.4 (DIN)
unnamed: RGB4.2 (DOUT), RGB5.4 (DIN)
unnamed: RGB5.2 (DOUT), RGB6.4 (DIN)
unnamed: RGB6.2 (DOUT), RGB7.4 (DIN)
unnamed: RGB7.2 (DOUT), RGB8.4 (DIN)
unnamed: RGB8.2 (DOUT), RGB9.4 (DIN)
unnamed: RGB10.2 (DOUT), RGB11.4 (DIN)
unnamed: RGB9.2 (DOUT), RGB10.4 (DIN)
unnamed: RGB11.2 (DOUT), RGB12.4 (DIN)
unnamed: RGB12.2 (DOUT), RGB13.4 (DIN)
unnamed: RGB13.2 (DOUT), RGB14.4 (DIN)
unnamed: RGB14.2 (DOUT), RGB15.4 (DIN)
unnamed: RGB15.2 (DOUT), RGB16.4 (DIN)
RGBLED: RC9.1, RGB1.4 (DIN)
RGBLED_3V3: U4.2; also elsewhere on the board

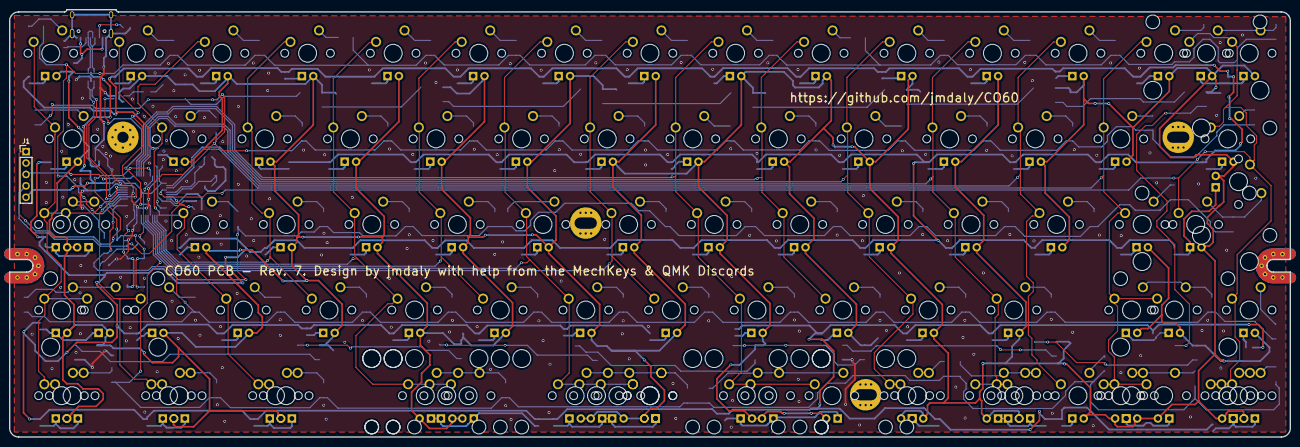
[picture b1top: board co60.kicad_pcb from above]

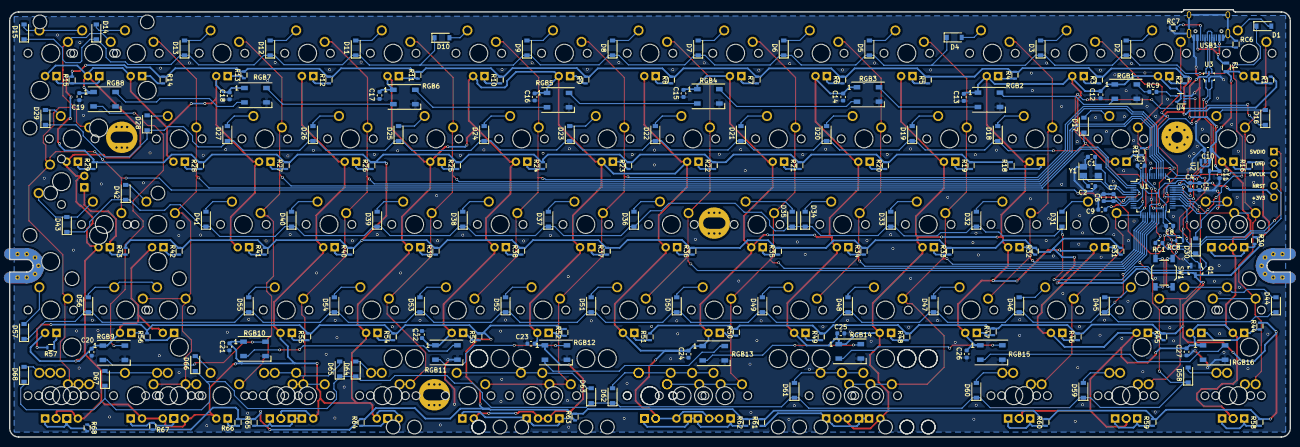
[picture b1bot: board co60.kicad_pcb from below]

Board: 2 copper layers, 285.0 x 95.1 mm, 285 parts (193 on the bottom side), 193 nets.

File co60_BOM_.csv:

References,Part,Value,Footprint,Quantity Per PCB,Digi-Key_PN,Datasheet,Description,Product,LCSC PN,Config,Category,Status,Family,MPN,DK_Datasheet_Link,DK_Detail_Page,Manufacturer,DigiKey Page
C3 C4 C8 C9 C12 C13 C14 C15 C16 C17 C18 C19 C20 C21 C22 C23 C24 C25 C26 C27,C,100n,C_0603_1608Metric,20,445-2500-1-ND,https://product.tdk.com/info/en/catalog/datasheets/mlcc_comm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,,C1608X8R1E104K080AA,C1590,,,,,,,,,
C7,C,10n,C_0603_1608Metric,1,,https://datasheet.lcsc.com/szlcsc/Samsung-Electro-Mechanics-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,,CL10B103KB8NNNC,C1589,,,,,,,,,
C6 C10 C11,C,1u,C_0603_1608Metric,3,445-13234-1-ND,https://product.tdk.com/info/en/catalog/datasheets/mlcc_comm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,,CGB3B3JB1C105K055AB,C59782,,,,,,,,,
C1 C2,C,30p,C_0603_1608Metric,2,,https://datasheet.lcsc.com/szlcsc/Samsung-Electro-Mechanics-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,,CL10C300JB8NNNC,C22397,,,,,,,,,
C5,C,4.7u,C_0603_1608Metric,1,1276-1900-1-ND,http://www.samsungsem.com/kr/support/product-search/mlcc/__i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,,CL10A475KA8NQNC,C19666,,,,,,,,,
D1 D2 D3 D4 D5 D6 D7 D8 D9 D10 D11 D12 D13 D14 D15 D16 D17 D18 D19 D20 D21 D22 D23 D24 D25 D26 D27 D28 D29 D30 D31 D32 D33 D34 D35 D36 D37 D38 D39 D40 D41 D42 D43 D44 D45 D46 D47 D48 D49 D50 D51 D52 D53 D54 D55 D56 D57 D58 D59 D60 D61 D62 D63 D64 D65 D66 D67 D68,D_Small,D_Small,D_SOD-123,68,1N4148WTPMSCT-ND,http://www.mccsemi.com/up_pdf/1N4148W(SOD123).pdf,,1N4148W-TP,C83528,,,,,,,,,
F1,Polyfuse_Small,500mA,R_0805,1,F2772CT-ND,http://www.littelfuse.com/~/media/electronics/datasheets/res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,,0805L050WR,C66452,,,,,,,,,
Q1,FMMT493TA,FMMT493TA,SOT-23-3,1,FMMT493CT-ND,https://www.diodes.com/assets/Datasheets/FMMT493.pdf,TRANS NPN 100V 1A SOT23-3,FMMT493TA,C47296,,Discrete Semiconductor Products,Active,Transistors - Bipolar (BJT) - Single,FMMT493TA,https://www.diodes.com/assets/Datasheets/FMMT493.pdf,/product-detail/en/diodes-incorporated/FMMT493TA/FMMT493CT-ND/92663,Diodes Incorporated,
R1 R2 R3 R4 R5 R6 R7 R8 R9 R10 R11 R12 R13 R14 R15 R16 R17 R18 R19 R20 R21 R22 R23 R24 R25 R26 R27 R28 R29 R30 R31 R32 R33 R34 R35 R36 R37 R38 R39 R40 R41 R42 R43 R44 R45 R46 R47 R48 R49 R50 R51 R52 R53 R54 R55 R56 R57 R58 R59 R60 R61 R62 R63 R64 R65 R66 R67 R68,R_Small,560,R_0603,68,MCT0603-560-CFCT-ND,https://www.mouser.ca/datasheet/2/427/mcx0x0xpro-223600.pdf,,MCT06030C5600FP500,C137619,,,,,,,,,
RC8,R,10k,R_0603,1,P10KGCT-ND,https://industrial.panasonic.com/ww/products/resistors/chip-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,,ERJ-3GEYJ103V,C98220,,,,,,,,,
RC1 RC9,R_Small,470,R_0603_1608Metric,2,,https://datasheet.lcsc.com/szlcsc/YAGEO-RC0603JR-07470RL_C11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,,RC0603JR-07470RL,C114433,,,,,,,,,
RC6 RC7,R,5.1k,R_0603,2,RMCF0603JT5K10CT-ND,https://www.seielect.com/Catalog/SEI-RMCF_RMCP.pdf,,RMCF0603JT5K10,C14677,,,,,,,,,
RGB1 RGB2 RGB3 RGB4 RGB5 RGB6 RGB7 RGB8 RGB9 RGB10 RGB11 RGB12 RGB13 RGB14 RGB15 RGB16,WS2812B,WS2812B,LED_WS2812B_PLCC4_5.0x5.0mm_P3.2mm,16,,https://cdn-shop.adafruit.com/datasheets/WS2812B.pdf,RGB LED with integrated controller,,C114585,,,,,,,,,
SW1,SW_Push,SW_Push,SW_SPST_TL3342,1,EG2531CT-ND,https://www.e-switch.com/system/asset/product_line/data_shee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,,TL3342F160QG/TR,C92584,,,,,,,,,https://www.digikey.ca/product-detail/en/e-switch/TL3342F160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
U4,74LVC1G34,74LVC1G34,SOT-353_SC-70-5,1,,,,,C94111,,,,,,,,,
U3,NUF2221W1T2G,NUF2221W1T2G,SOT-363,1,,http://www.onsemi.com/pub/Collateral/NUF2221W1T2-D.PDF,,,C274624,,,,,,,,,
U1,STM32F303CBTx,STM32F303CBTx,LQFP-48_7x7mm_Pitch0.5mm,1,,http://www.st.com/st-web-ui/static/active/en/resource/techni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,"ARM Cortex-M4 MCU, 128KB flash, 32KB RAM, 72MHz, 2-3.6V, 37 GPIO, LQFP-48",,C108516,,,,,,,,,
U2,TLV70233_SOT23-5,TLV70233_SOT23-5,SOT-23-5,1,,http://www.ti.com/lit/ds/symlink/tlv702.pdf,"300 mA Low Dropout Voltage Regulator, Fixed Output 3.3V, SOT-23-5",,C26833,,,,,,,,,
USB1,HRO-TYPE-C-31-M-12,HRO-TYPE-C-31-M-12,HRO-TYPE-C-31-M-12-Assembly,1,,https://datasheet.lcsc.com/szlcsc/Korean-Hroparts-Elec-TYPE-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,,,C165948,,,,,,,,,
Y1,Crystal_GND24,8MHz,Crystal_SMD_5032-4pin_5.0x3.2mm,1,,https://lcsc.com/product-detail/SMD-Crystals_SMD-5032-4P-8M-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,,Zhejiang Abel Elec SMD-5032_4P8M20pf20ppm,C133333,,,,,,,,,





Component Groups:,38
Component Count:,285
Fitted Components:,193
Number of PCBs:,1
Total components:,193
Schematic Version:,
Schematic Date:,
BoM Date:,Tue 15 Jan 2019 10:27:23 PM UTC
Schematic Source:,/home/q_user/git/CO60/co60.sch
KiCad Version:,Eeschema 5.0.1-33cea8e~67~ubuntu16.04.1
